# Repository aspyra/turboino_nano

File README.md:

# turboino_nano
SAMC21E development board compatible with Arduino Nano

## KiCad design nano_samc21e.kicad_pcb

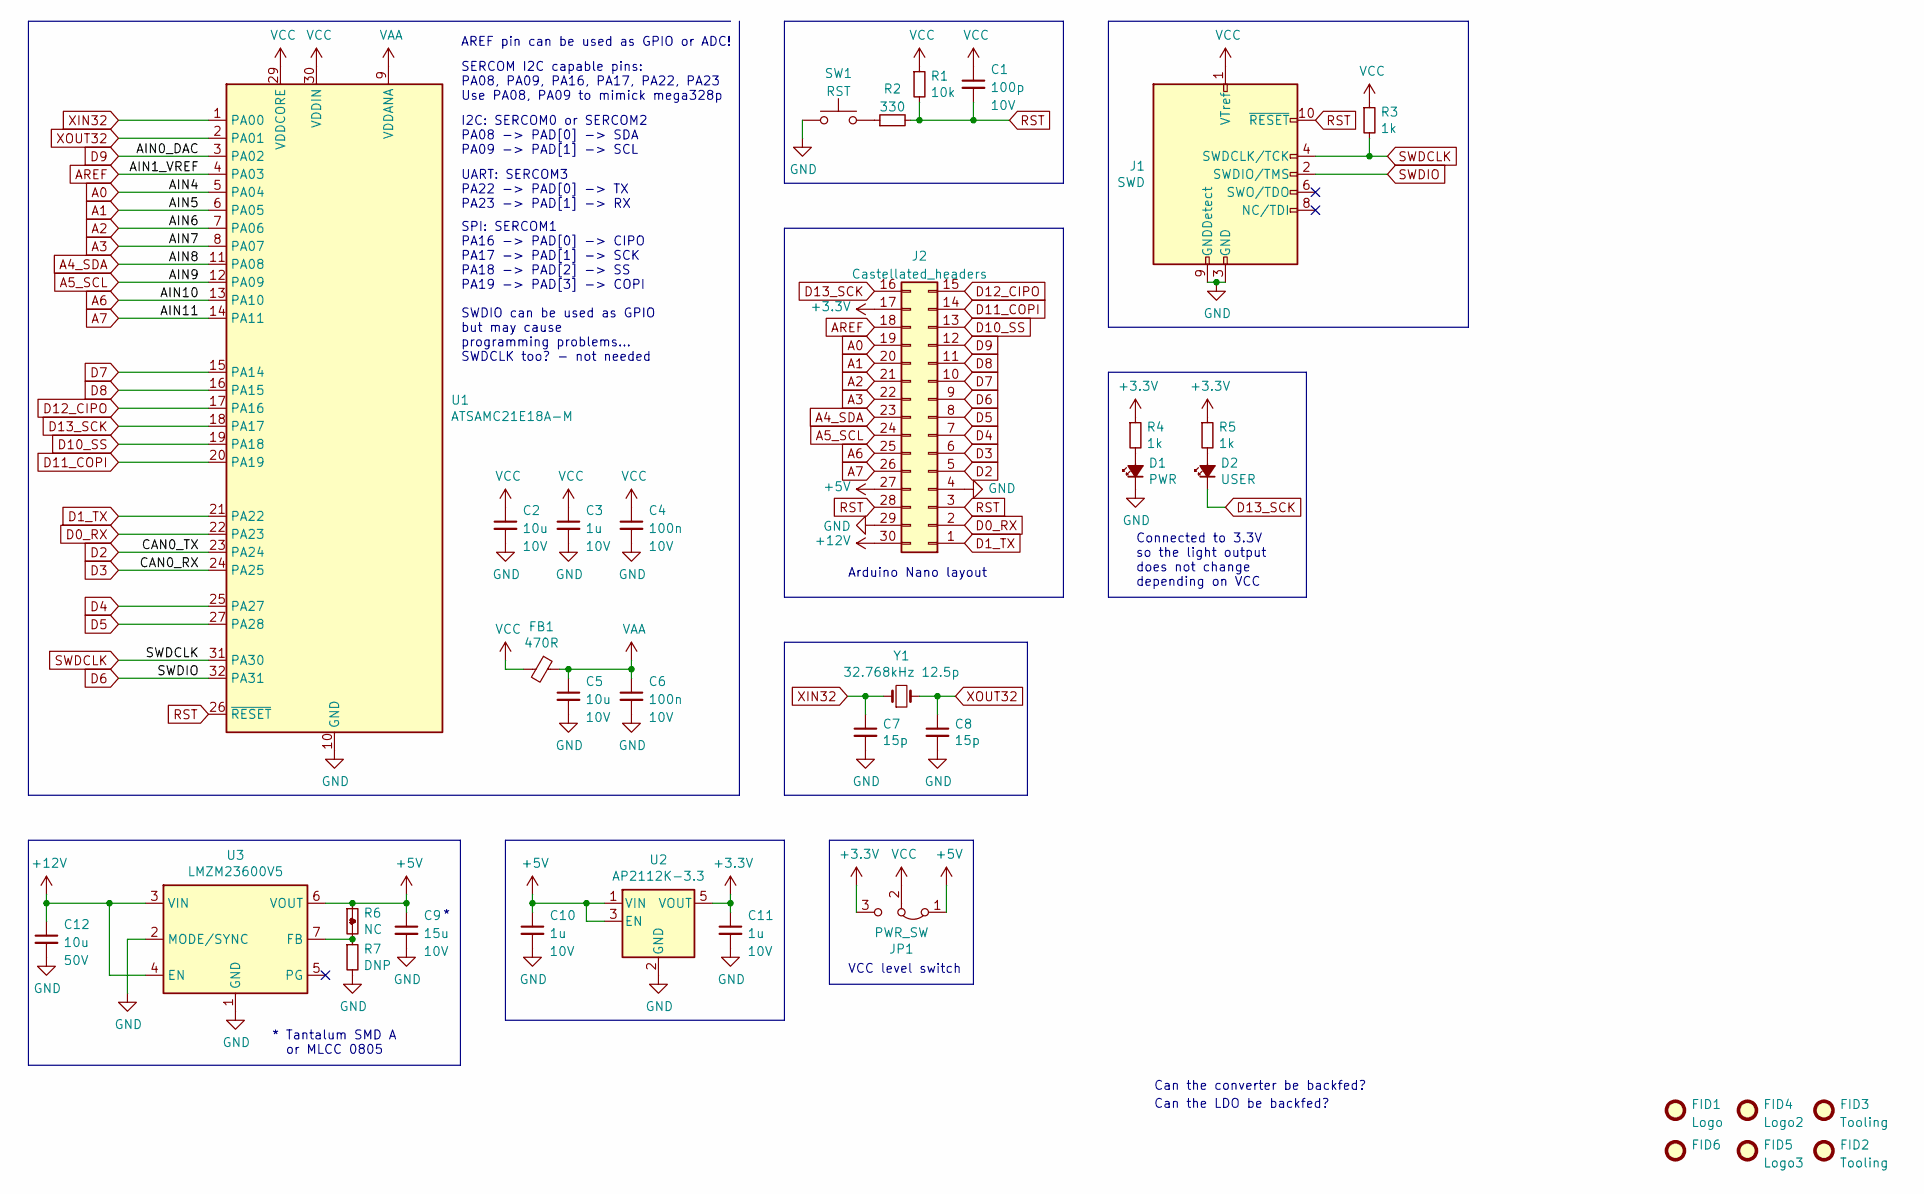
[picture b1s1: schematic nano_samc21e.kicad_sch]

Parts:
C1: 100p; 0402_minimalist; Rating 10V
C2, C5: 10u; 0603_minimalist; Rating 10V
C3, C10, C11: 1u; 0402_minimalist; Rating 10V
C4, C6: 100n; 0402_minimalist; Rating 10V
C7, C8: 15p; 0402_minimalist
C9: 15u; C_1206_3216Metric; Rating 10V
C12: 10u; C_1210_3225Metric; Rating 50V
D1: PWR; LED_0603_1608Metric
D2: USER; LED_0603_1608Metric
FB1: 470R; 0603_minimalist
FID1: Logo
FID2, FID3: Tooling; JLCPCB_tooling_hole
FID4: Logo2; turboino_logo
FID5: Logo3; turboino_back
FID6: (no value)
J1: SWD; PinHeader_2x05_P1.27mm_Vertical_SMD
J2: Castellated_headers; Arduino_Nano
JP1: PWR_SW; PinHeader_1x03_P2.54mm_Vertical
R1: 10k; 0402_minimalist
R2: 330; 0402_minimalist
R3, R4, R5: 1k; 0402_minimalist
R6: NC; 0402_NC_minimalist
R7: DNP; 0402_minimalist
SW1: RST; SW_SPST_SKQG_WithStem
U1: ATSAMC21E18A-M; QFN-32-1EP_5x5mm_P0.5mm_EP3.6x3.6mm
U2: AP2112K-3.3; SOT-23-5
U3: LMZM23600V5; LMZM2360X
Y1: 32.768kHz 12.5p; Crystal_SMD_3215-2Pin_3.2x1.5mm

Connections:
+3V3: C11.1, J2.17, JP1.3 (B), R4.1, R5.1, U2.5 (VOUT)
+5V: C9.1, C10.1, J2.27, JP1.1 (A), R6.1, U2.1 (VIN), U2.3 (EN), U3.6 (VOUT)
+12V: C12.1, J2.30, U3.3 (VIN), U3.4 (EN)
A0: J2.19, U1.5 (PA04)
A1: J2.20, U1.6 (PA05)
A2: J2.21, U1.7 (PA06)
A3: J2.22, U1.8 (PA07)
A4_SDA: J2.23, U1.11 (PA08)
A5_SCL: J2.24, U1.12 (PA09)
A6: J2.25, U1.13 (PA10)
A7: J2.26, U1.14 (PA11)
AREF: J2.18, U1.4 (PA03)
D0_RX: J2.2, U1.22 (PA23)
D1_TX: J2.1, U1.21 (PA22)
D2: J2.5, U1.23 (PA24)
D3: J2.6, U1.24 (PA25)
D4: J2.7, U1.25 (PA27)
D5: J2.8, U1.27 (PA28)
D6: J1.2 (SWDIO/TMS), J2.9, U1.32 (PA31)
D7: J2.10, U1.15 (PA14)
D8: J2.11, U1.16 (PA15)
D9: J2.12, U1.3 (PA02)
D10_SS: J2.13, U1.19 (PA18)
D11_COPI: J2.14, U1.20 (PA19)
D12_CIPO: J2.15, U1.17 (PA16)
D13_SCK: D2.1 (K), J2.16, U1.18 (PA17)
GND: C2.2, C3.2, C4.2, C5.2, C6.2, C7.2, C8.2, C9.2, C10.2, C11.2, C12.2, D1.1 (K), J1.3 (GND), J1.5 (GND), J1.9 (GNDDetect), J2.4, J2.29, R7.2, SW1.1, U1.10 (GND), U1.28 (GND), U2.2 (GND), U3.1 (GND), U3.2 (MODE/SYNC), U3.11 (GND)
unnamed: D1.2 (A), R4.2
unnamed: D2.2 (A), R5.2
unnamed: R2.1, SW1.2
unnamed: R6.2, R7.1, U3.7 (FB)
RST: C1.2, J1.10 (~RESET), J2.3, J2.28, R1.2, R2.2, U1.26 (~RESET)
SWDCLK: J1.4 (SWDCLK/TCK), R3.2, U1.31 (PA30)
VAA: C5.1, C6.1, FB1.1, U1.9 (VDDANA)
VCC: C1.1, C2.1, C3.1, C4.1, FB1.2, J1.1 (VTref), JP1.2 (C), R1.1, R3.1, U1.29 (VDDCORE), U1.30 (VDDIN)
XIN32: C7.1, U1.1 (PA00), Y1.1
XOUT32: C8.1, U1.2 (PA01), Y1.2

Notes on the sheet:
VCC level switch
UART: SERCOM3 PA22 -> PAD[0] -> TX PA23 -> PAD[1] -> RX
SPI: SERCOM1 PA16 -> PAD[0] -> CIPO PA17 -> PAD[1] -> SCK PA18 -> PAD[2] -> SS PA19 -> PAD[3] -> COPI
I2C: SERCOM0 or SERCOM2 PA08 -> PAD[0] -> SDA PA09 -> PAD[1] -> SCL
Arduino Nano layout
AREF pin can be used as GPIO or ADC!
SERCOM I2C capable pins: PA08, PA09, PA16, PA17, PA22, PA23 Use PA08, PA09 to mimick mega328p
* Tantalum SMD A or MLCC 0805
SWDIO can be used as GPIO but may cause programming problems... SWDCLK too? - not needed
Connected to 3.3V so the light output does not change depending on VCC
Can the converter be backfed?
Can the LDO be backfed?

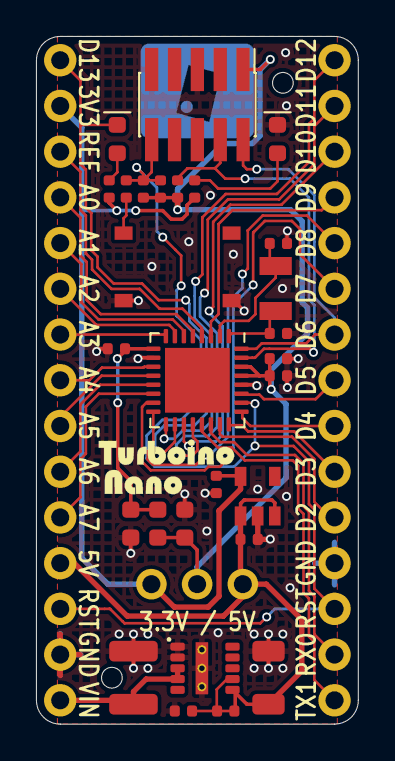
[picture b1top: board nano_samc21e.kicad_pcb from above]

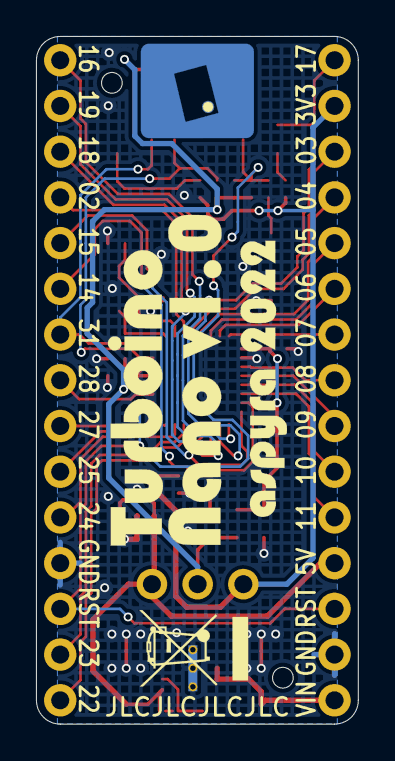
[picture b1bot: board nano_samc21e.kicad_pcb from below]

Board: 2 copper layers, 17.9 x 38.2 mm, 36 parts (3 on the bottom side), 37 nets.

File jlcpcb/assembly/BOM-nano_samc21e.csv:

Comment,Designator,Footprint,LCSC
470R,FB1,0603_minimalist,C1002
1k,"R3,R4,R5",0402_minimalist,C11702
100n,"C4,C6",0402_minimalist,C1525
100p,C1,0402_minimalist,C1546
15p,"C7,C8",0402_minimalist,C1548
10u,"C2,C5",0603_minimalist,C19702
330,R2,0402_minimalist,C25104
10k,R1,0402_minimalist,C25744
RST,SW1,SW_SPST_SKQG_WithStem,C318884
32.768kHz 12.5p,Y1,Crystal_SMD_3215-2Pin_3.2x1.5mm,C32346
1u,"C10,C11,C3",0402_minimalist,C52923
PWR,"D1,D2",LED_0603_1608Metric,C72038
Castellated_headers,J2,Arduino_Nano,
SWD,J1,PinHeader_2x05_P1.27mm_Vertical_SMD,
ATSAMC21E18A-M,U1,QFN-32-1EP_5x5mm_P0.5mm_EP3.6x3.6mm,
15u,C9,C_1206_3216Metric,
10u,C12,C_1210_3225Metric,
NC,R6,0402_NC_minimalist,
DNP,R7,0402_minimalist,
LMZM23600V5,U3,LMZM2360X,
PWR_SW,JP1,PinHeader_1x03_P2.54mm_Vertical,
AP2112K-3.3,U2,SOT-23-5,
Logo,FID1,Logo,
Tooling,FID2,JLCPCB_tooling_hole,
Tooling,FID3,JLCPCB_tooling_hole,
Logo2,FID4,turboino_logo,
Logo3,FID5,turboino_back,
WEEE,FID6,WEEE-Logo_4.2x6mm_SilkScreen,

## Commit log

2022-04-27 First commit - schematic more or less done, starting 4 layer layout
2022-05-02 Massive rework: - 2 layer PCB - design restraints set according to JLCPCB capabilites - no castellated holes, smaller board dimensions - Arduino style numbering on top silkscreen - Changed footprints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
2022-05-03 v1.0 finished - layout and routing finished - added front and back graphics, JLCPCB tooling holes
2022-05-03 Generated JLCPCB output files
2022-05-03 Added missing pin numbering Added WEEE logo Added JLCPCB order number Generated fresh JLCPCB output files
